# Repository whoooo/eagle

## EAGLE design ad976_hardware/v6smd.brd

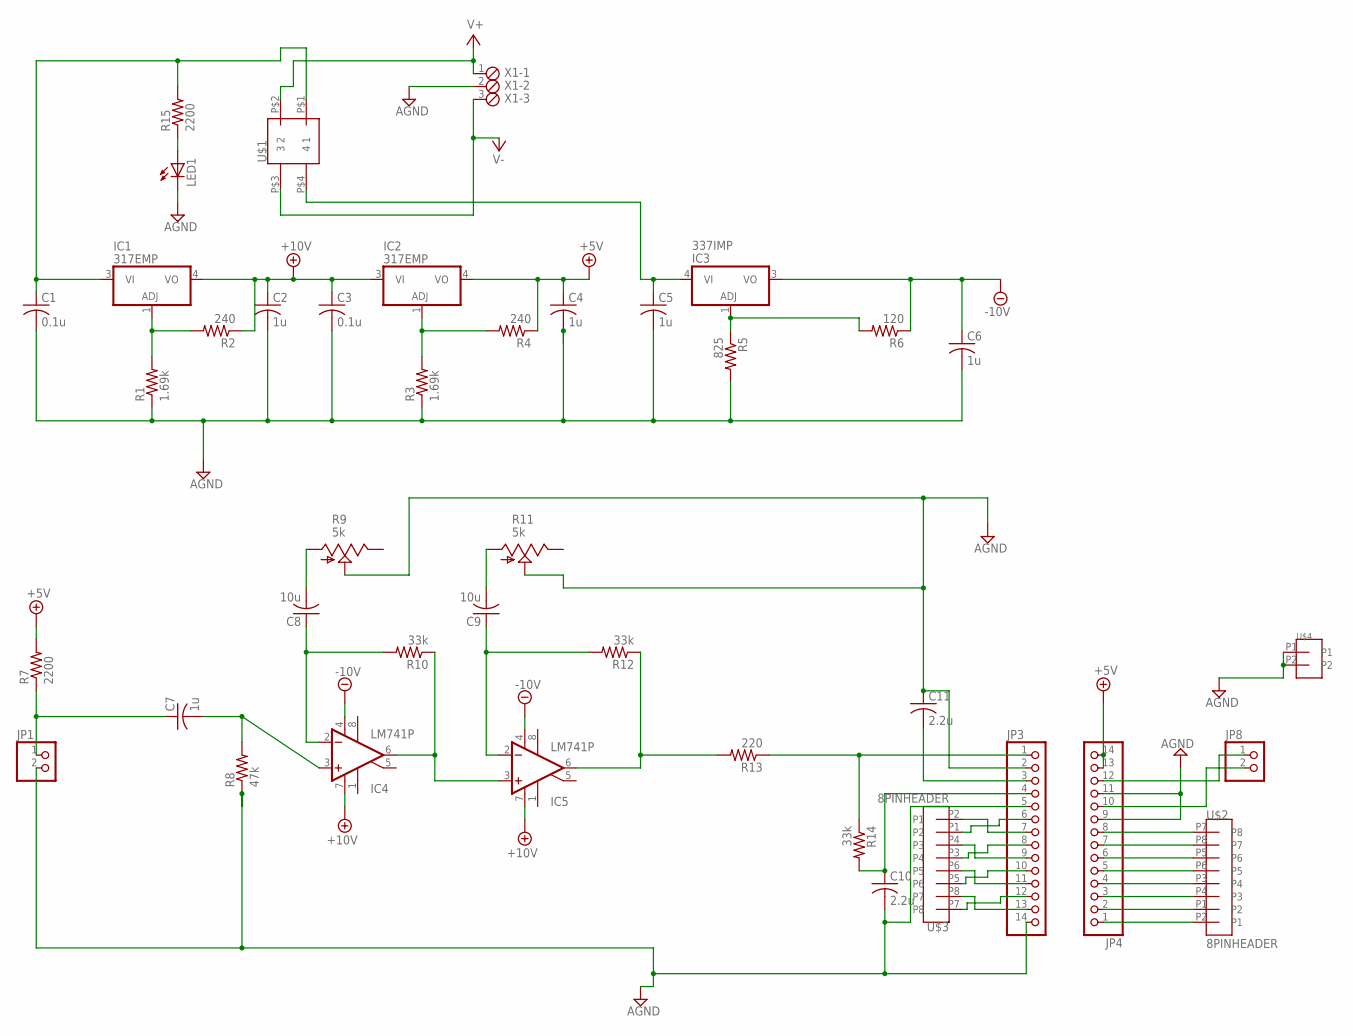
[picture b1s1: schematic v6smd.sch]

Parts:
C1, C3: 0.1u; C1206
C2, C4, C5, C6, C7: 1u; C1206
C8, C9: 10u; C1206
C10, C11: 2.2u; C1206
IC1, IC2: 317EMP; SOT223
IC3: 337IMP; SOT223
IC4, IC5: LM741P; DIL08
JP1, JP8: PINHD-1X2; 1X02
JP3, JP4: PINHD-1X14; 1X14
LED1: LED3MM
R1, R3: 1.69k; R2512
R2, R4: 240; R2512
R5: 825; R2512
R6: 120; R2512
R7, R15: 2200; R2512
R8: 47k; R2512
R9, R11: 5k; B64Y
R10, R12, R14: 33k; R2512
R13: 220; R2512
U$1: S201031MS02Q; DPST_FOOTPRINT
U$2, U$3: 8PINHEADER; 2X4HEADER
U$4: 2X1HEADER
X1: MPT3; 3POL254

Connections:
+5V: C4.1, IC2.4 (VO), JP4.13, JP4.14, R4.1, R7.2
+10V: C2.1, C3.1, IC1.4 (VO), IC2.3 (VI), IC4.7 (V+), IC5.7 (V+), R2.1
-10V: C6.1, IC3.3 (VO), IC4.4 (V-), IC5.4 (V-), R6.1
AGND: C1.2, C2.2, C3.2, C4.2, C5.2, C6.2, C10.2, C11.1, JP1.2, JP3.2, JP3.5, JP3.14, JP4.9, JP4.11, LED1.K (C), R1.1, R3.1, R5.2, R8.1, R9.S, R11.S, U$4.P1, U$4.P2, X1.2
unnamed: IC4.6 (OUT), IC5.3 (+IN), R10.1
unnamed: C7.1, JP1.1, R7.1
unnamed: C7.2, IC4.3 (+IN), R8.2
unnamed: C8.1, IC4.2 (-IN), R10.2
unnamed: IC5.6 (OUT), R12.1, R13.2
unnamed: C9.1, IC5.2 (-IN), R12.2
unnamed: JP3.1, R13.1, R14.1
unnamed: IC1.1 (ADJ), R1.2, R2.2
unnamed: IC2.1 (ADJ), R3.2, R4.2
unnamed: IC3.1 (ADJ), R5.1, R6.2
unnamed: C8.2, R9.A
unnamed: JP4.1, U$2.P2 (P1)
unnamed: JP4.2, U$2.P1 (P2)
unnamed: C9.2, R11.A
unnamed: C11.2, JP3.3
unnamed: C10.1, JP3.4, R14.2
unnamed: JP4.3, U$2.P4 (P3)
unnamed: JP4.4, U$2.P3 (P4)
unnamed: JP4.5, U$2.P6 (P5)
unnamed: JP4.6, U$2.P5 (P6)
unnamed: JP4.7, U$2.P8 (P7)
unnamed: JP4.8, U$2.P7 (P8)
unnamed: JP3.7, U$3.P2 (P1)
unnamed: JP3.6, U$3.P1 (P2)
unnamed: JP3.12, U$3.P7 (P8)
unnamed: JP3.13, U$3.P8 (P7)
unnamed: JP3.11, U$3.P6 (P5)
unnamed: JP3.9, U$3.P4 (P3)
unnamed: JP3.10, U$3.P5 (P6)
unnamed: JP3.8, U$3.P3 (P4)
unnamed: JP4.12, JP8.1
unnamed: JP4.10, JP8.2
unnamed: C1.1, IC1.3 (VI), R15.2, U$1.P$1 (1)
unnamed: C5.1, IC3.4 (VI), U$1.P$4 (4)
unnamed: LED1.A, R15.1
V+: U$1.P$2 (2), X1.1
V-: U$1.P$3 (3), X1.3

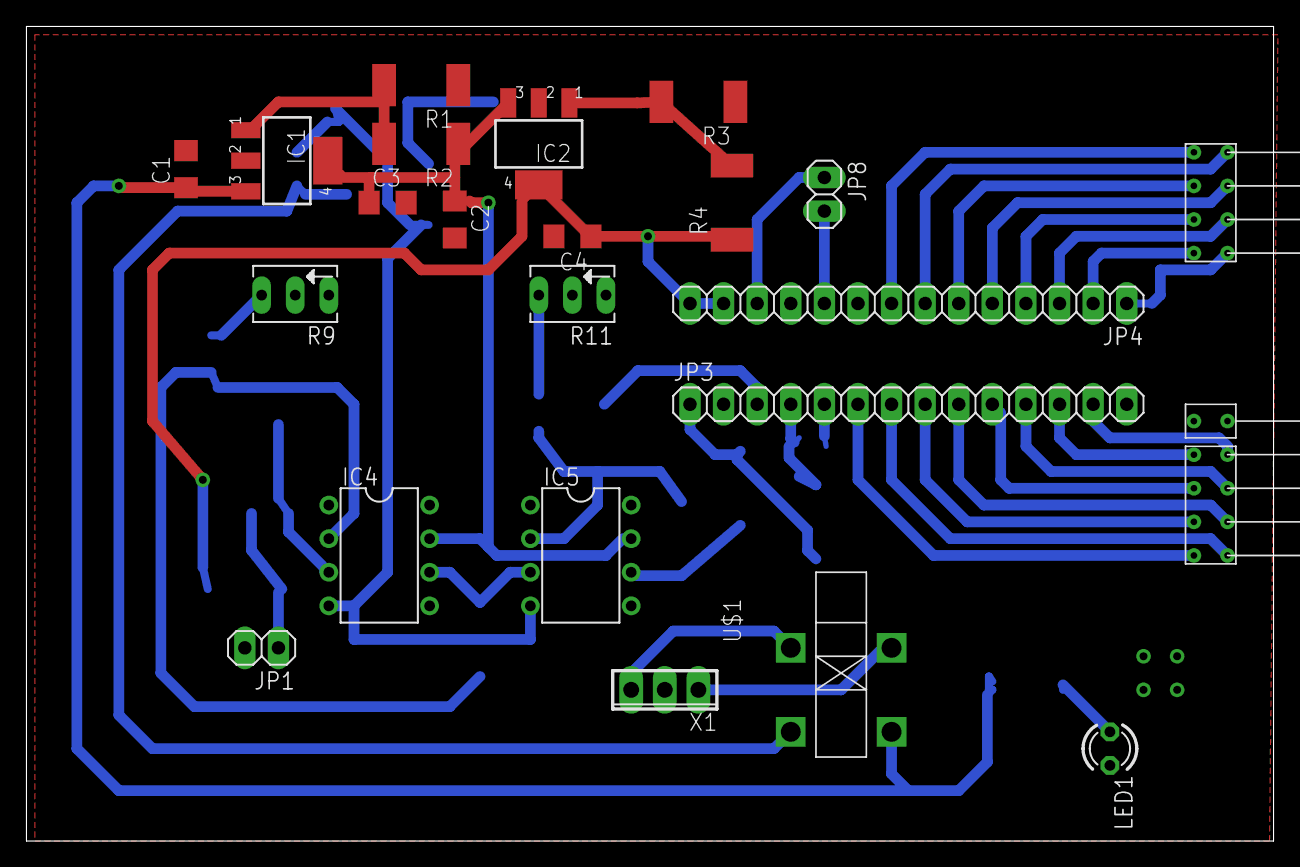
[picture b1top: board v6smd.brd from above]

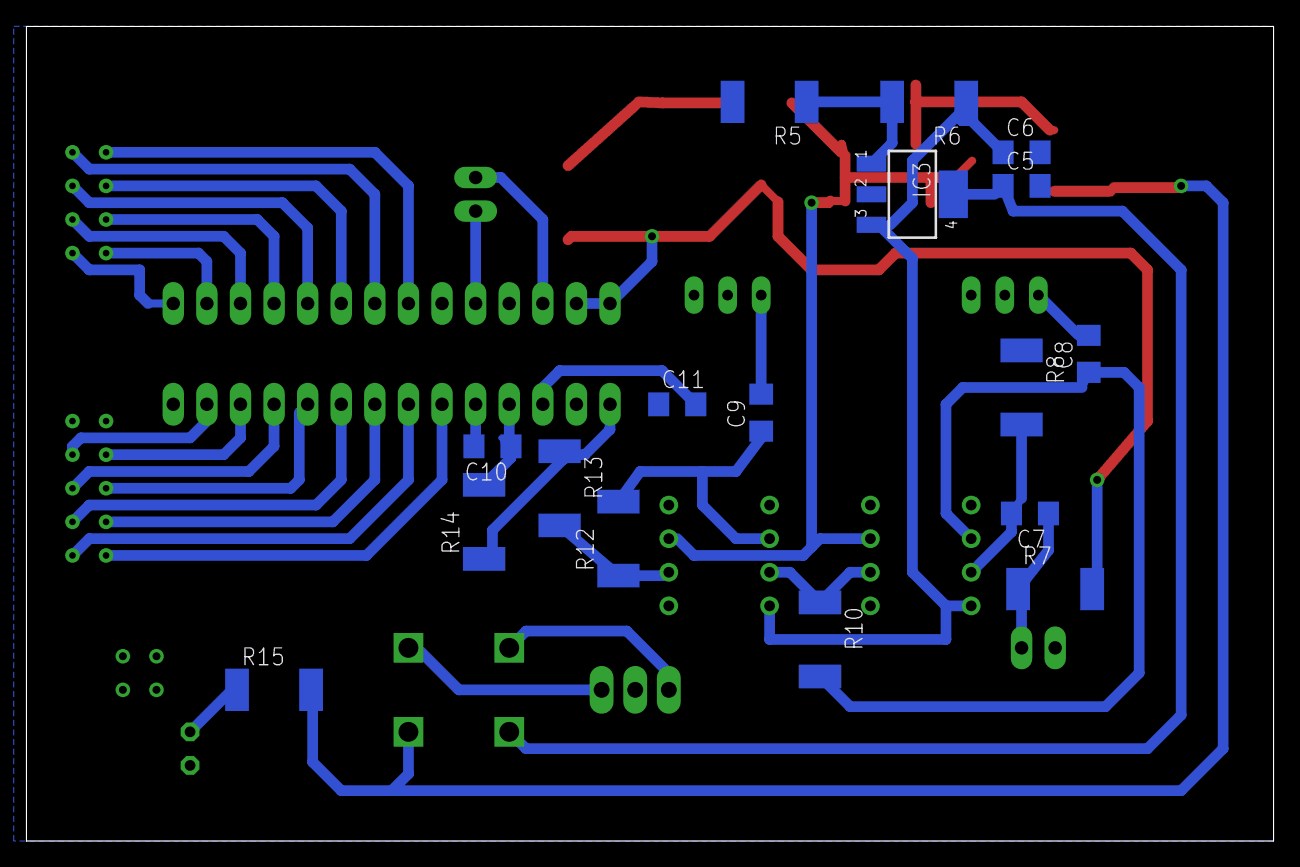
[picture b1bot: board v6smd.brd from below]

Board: 2 copper layers, 94.3 x 61.6 mm, 41 parts (17 on the bottom side), 41 nets.

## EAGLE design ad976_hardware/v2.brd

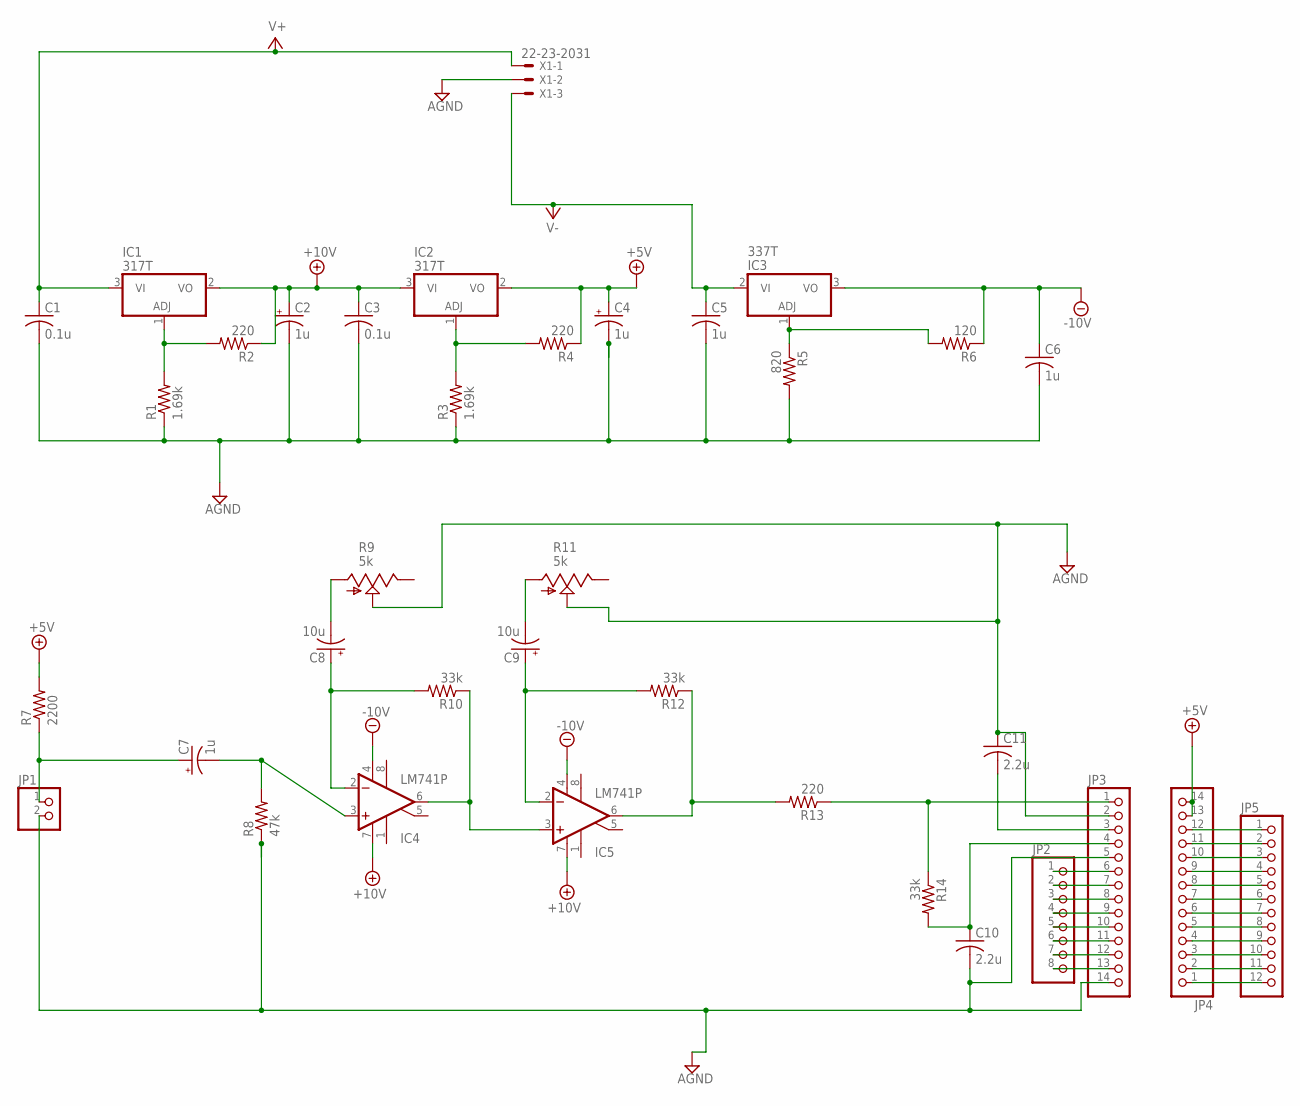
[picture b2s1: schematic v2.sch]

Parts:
C1, C3: 0.1u; C050-045X075
C2, C4, C7: 1u; E2,5-5
C5, C6: 1u; C050-045X075
C8, C9: 10u; E2,5-5
C10, C11: 2.2u; C050-045X075
IC1, IC2: 317T; TO220H
IC3: 337T; TO220H
IC4, IC5: LM741P; DIL08
JP1: PINHD-1X2; 1X02
JP2: PINHD-1X8; 1X08
JP3, JP4: PINHD-1X14; 1X14
JP5: PINHD-1X12; 1X12
R1, R3: 1.69k; 0207/10
R2, R4, R13: 220; 0207/10
R5: 820; 0207/10
R6: 120; 0207/10
R7: 2200; 0207/10
R8: 47k; 0207/10
R9, R11: 5k; CA6V
R10, R12, R14: 33k; 0207/10
X1: 22-23-2031

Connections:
+5V: C4.+, IC2.2 (VO), JP4.13, JP4.14, R4.1, R7.2
+10V: C2.+, C3.1, IC1.2 (VO), IC2.3 (VI), IC4.7 (V+), IC5.7 (V+), R2.1
-10V: C6.1, IC3.3 (VO), IC4.4 (V-), IC5.4 (V-), R6.1
AGND: C1.2, C2.-, C3.2, C4.-, C5.2, C6.2, C10.2, C11.1, JP1.2, JP3.2, JP3.5, JP3.14, R1.1, R3.1, R5.2, R8.1, R9.S, R11.S, X1.2
unnamed: IC4.6 (OUT), IC5.3 (+IN), R10.1
unnamed: C7.+, JP1.1, R7.1
unnamed: C7.-, IC4.3 (+IN), R8.2
unnamed: C8.+, IC4.2 (-IN), R10.2
unnamed: IC5.6 (OUT), R12.1, R13.2
unnamed: C9.+, IC5.2 (-IN), R12.2
unnamed: JP3.1, R13.1, R14.1
unnamed: IC1.1 (ADJ), R1.2, R2.2
unnamed: IC2.1 (ADJ), R3.2, R4.2
unnamed: IC3.1 (ADJ), R5.1, R6.2
unnamed: C8.-, R9.A
unnamed: C9.-, R11.A
unnamed: C11.2, JP3.3
unnamed: C10.1, JP3.4, R14.2
unnamed: JP2.8, JP3.13
unnamed: JP2.7, JP3.12
unnamed: JP2.6, JP3.11
unnamed: JP2.5, JP3.10
unnamed: JP2.4, JP3.9
unnamed: JP2.3, JP3.8
unnamed: JP2.2, JP3.7
unnamed: JP2.1, JP3.6
unnamed: JP4.1, JP5.12
unnamed: JP4.2, JP5.11
unnamed: JP4.3, JP5.10
unnamed: JP4.4, JP5.9
unnamed: JP4.5, JP5.8
unnamed: JP4.6, JP5.7
unnamed: JP4.7, JP5.6
unnamed: JP4.8, JP5.5
unnamed: JP4.9, JP5.4
unnamed: JP4.10, JP5.3
unnamed: JP4.11, JP5.2
unnamed: JP4.12, JP5.1
V+: C1.1, IC1.3 (VI), X1.1
V-: C5.1, IC3.2 (VI), X1.3

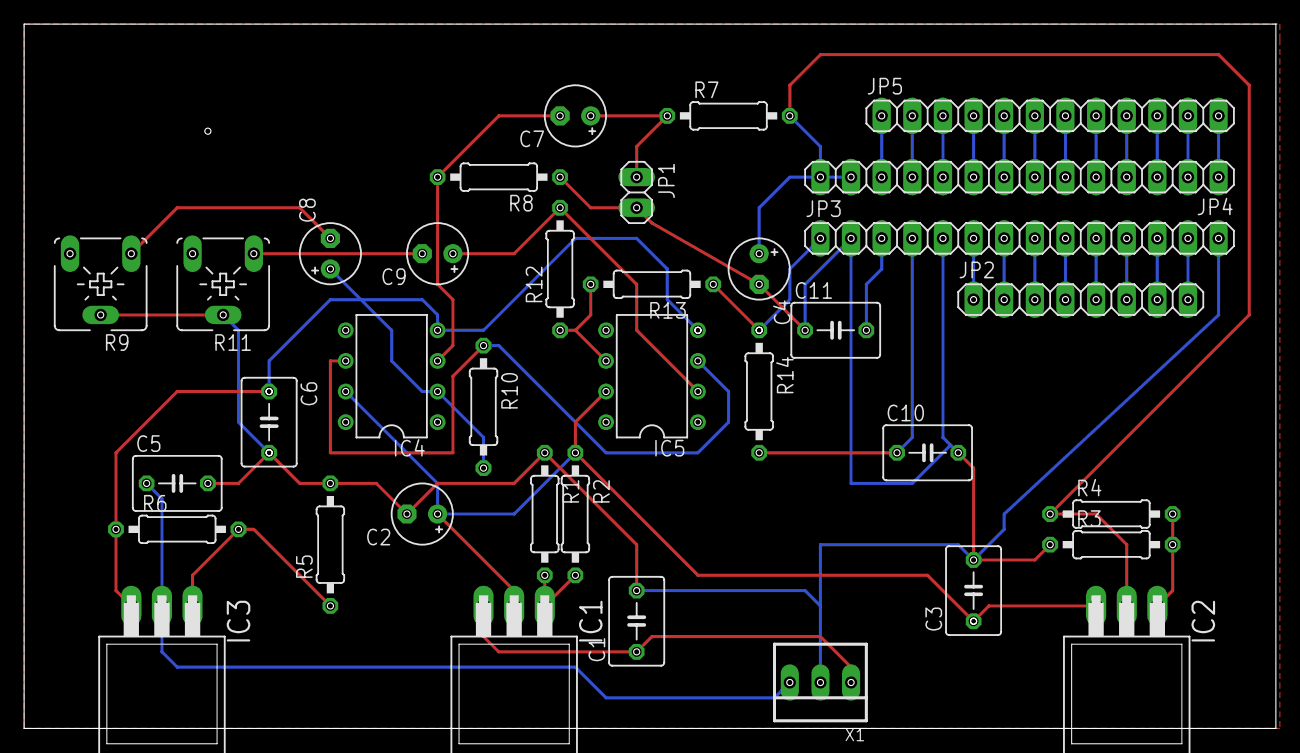
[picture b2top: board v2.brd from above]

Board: 2 copper layers, 103.8 x 58.4 mm, 36 parts (0 on the bottom side), 40 nets.

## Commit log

2015-03-18 :octocat: Added .gitattributes & .gitignore files
2015-03-18 initial
2015-03-18 update
    updated eagle schematic and pcam layout
2015-04-16 board updates
    reduced trace-gnd plane spacing, increased trace width
